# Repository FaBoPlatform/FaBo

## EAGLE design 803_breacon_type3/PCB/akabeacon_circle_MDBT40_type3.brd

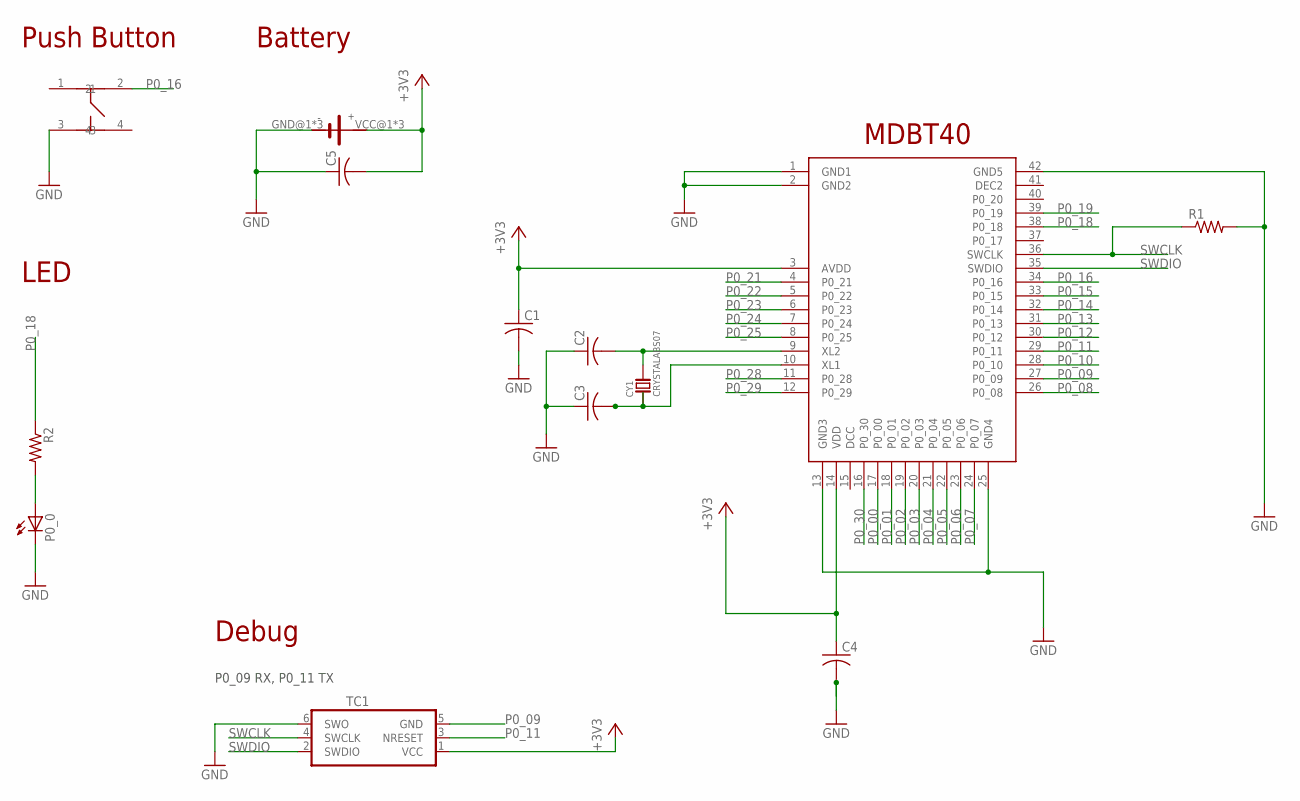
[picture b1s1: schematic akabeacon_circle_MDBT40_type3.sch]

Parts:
C1, C2, C3, C4, C5: C-USC0603; C0603
CY1: CRYSTALABS07; ABRACOM-ABS07-32.768KHZ
P0_0: LEDCHIP-LED0603; CHIP-LED0603
R1, R2: R-US_R0603; R0603
TC1: TC2030-IDC-NL
U$1: RAYTAC-MDBT40
U$3: SQUARE-TYPE3
U$5: SWICTH-4P(KMR2); SWITCH-4P(KMR2)

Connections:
+3V3: C1.1, C4.1, C5.2, TC1.1 (VCC), U$1.3 (AVDD), U$1.14 (VDD), U$3.VCC@1 (VCC), U$3.VCC@2 (VCC), U$3.VCC@3 (VCC)
GND: C1.2, C2.1, C3.1, C4.2, C5.1, P0_0.C, R1.2, TC1.6 (SWO), U$1.1 (GND1), U$1.2 (GND2), U$1.13 (GND3), U$1.25 (GND4), U$1.42 (GND5), U$3.GND@1 (GND), U$3.GND@2 (GND), U$3.GND@3 (GND), U$5.3
unnamed: P0_0.A, R2.2
unnamed: C2.2, CY1.P$2, U$1.9 (XL2)
unnamed: C3.2, CY1.P$1, U$1.10 (XL1)
P0_00: U$1.17 (P0_00)
P0_01: U$1.18 (P0_01)
P0_02: U$1.19 (P0_02)
P0_03: U$1.20 (P0_03)
P0_04: U$1.21 (P0_04)
P0_05: U$1.22 (P0_05)
P0_06: U$1.23 (P0_06)
P0_07: U$1.24 (P0_07)
P0_08: U$1.26 (P0_08)
P0_09: TC1.5 (GND), U$1.27 (P0_09)
P0_10: U$1.28 (P0_10)
P0_11: TC1.3 (NRESET), U$1.29 (P0_11)
P0_12: U$1.30 (P0_12)
P0_13: U$1.31 (P0_13)
P0_14: U$1.32 (P0_14)
P0_15: U$1.33 (P0_15)
P0_16: U$1.34 (P0_16), U$5.2
P0_18: R2.1, U$1.38 (P0_18)
P0_19: U$1.39 (P0_19)
P0_21: U$1.4 (P0_21)
P0_22: U$1.5 (P0_22)
P0_23: U$1.6 (P0_23)
P0_24: U$1.7 (P0_24)
P0_25: U$1.8 (P0_25)
P0_28: U$1.11 (P0_28)
P0_29: U$1.12 (P0_29)
P0_30: U$1.16 (P0_30)
SWCLK: R1.1, TC1.4 (SWCLK), U$1.36 (SWCLK)
SWDIO: TC1.2 (SWDIO), U$1.35 (SWDIO)

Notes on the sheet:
Battery
Push Button
MDBT40
LED
Debug
P0_09 RX, P0_11 TX

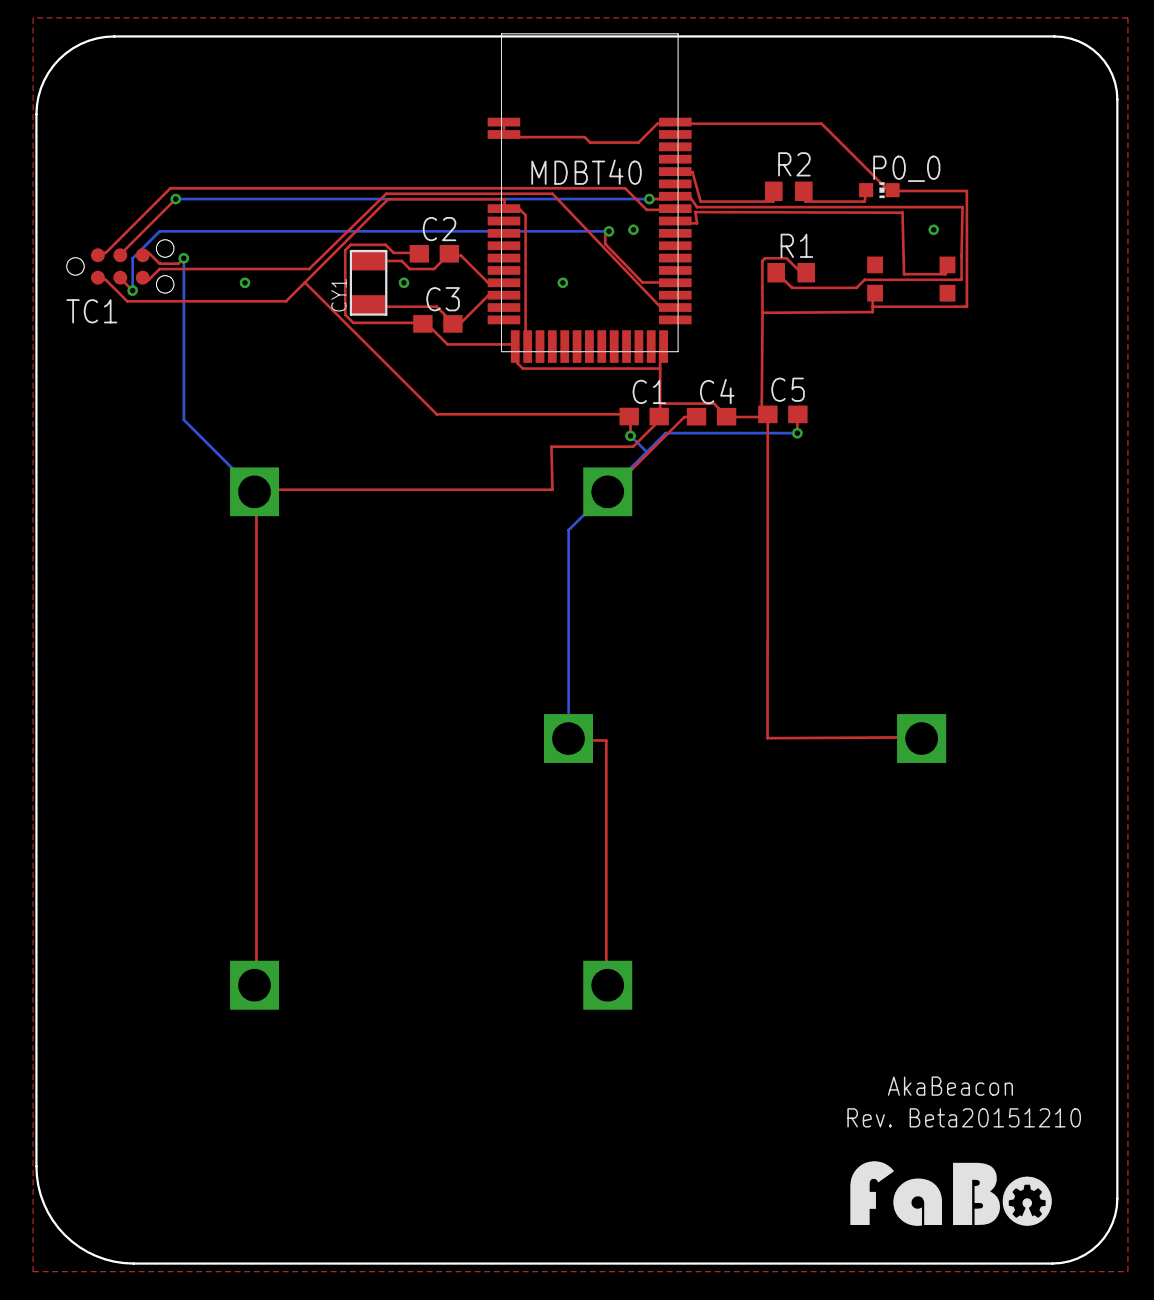
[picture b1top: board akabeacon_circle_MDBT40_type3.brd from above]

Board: 2 copper layers, 61.2 x 69.5 mm, 14 parts (0 on the bottom side), 11 nets.

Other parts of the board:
U$2: LOGO_FABO_M

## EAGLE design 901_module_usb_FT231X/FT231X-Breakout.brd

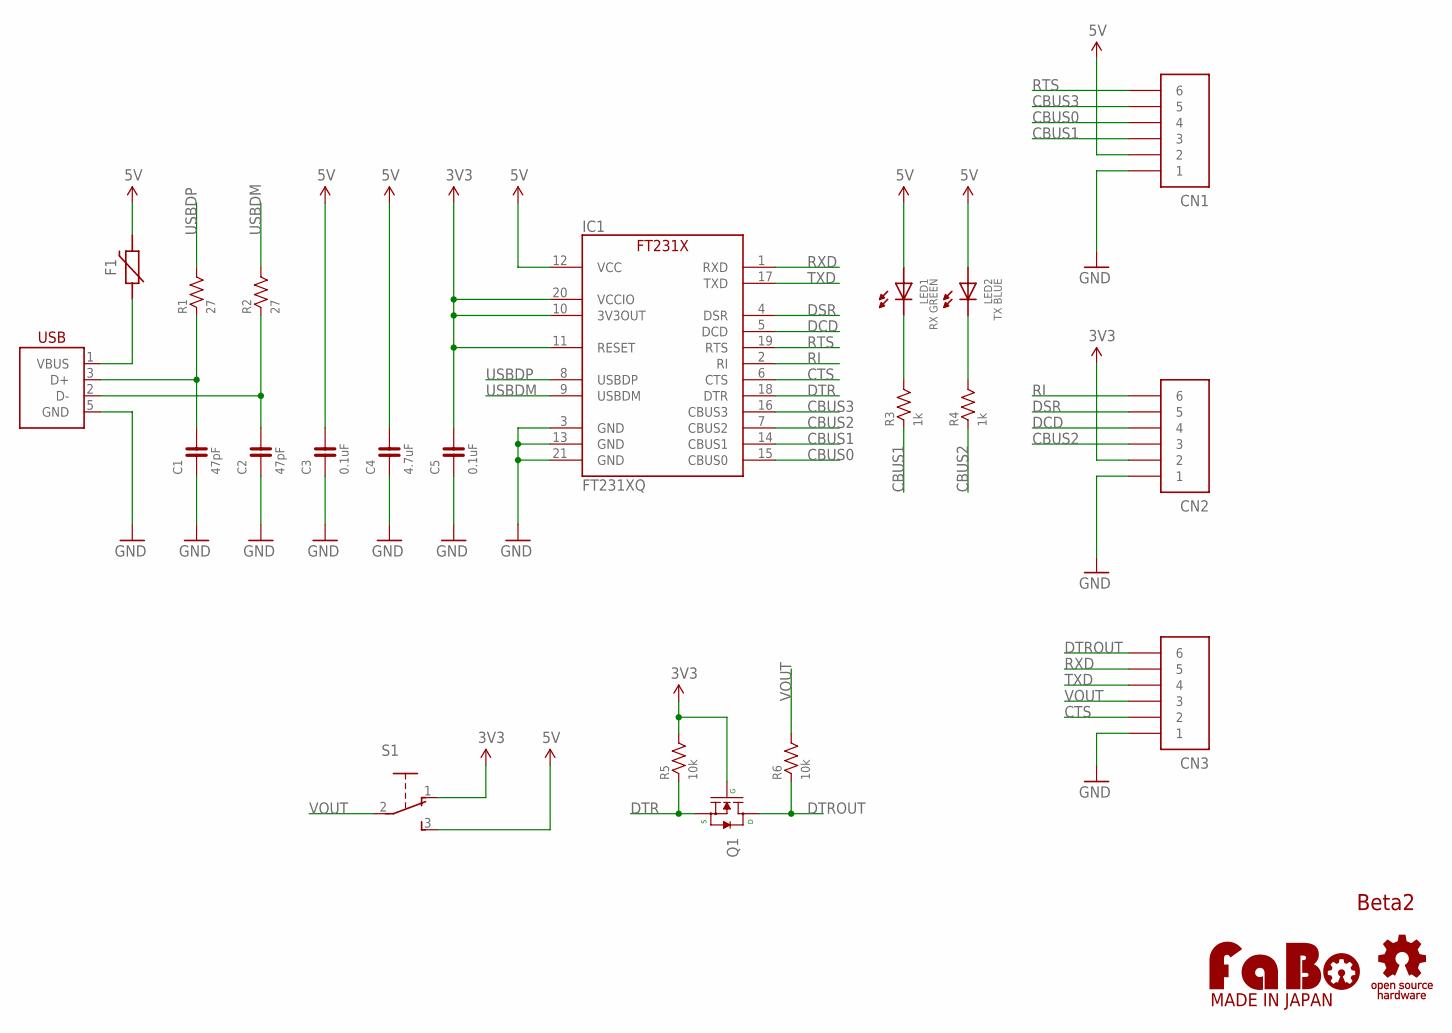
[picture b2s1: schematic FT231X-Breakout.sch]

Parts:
C1, C2: 47pF; 0603-NARROW
C3, C5: 0.1uF; 0603-NARROW
C4: 4.7uF; 0603-NARROW
CN1, CN2, CN3: PIN_HEADER_1X6; PIN_1X6
F1: POLYSWITCH; EIA0603
IC1: FT231XQ; QFN-20_FT231X
LED1: RX GREEN; 0603-NARROW
LED2: TX BLUE; 0603-NARROW
Q1: MOSFET-N; SOT23-3
R1, R2: 27; 0603-NARROW
R3, R4: 1k; 0603-NARROW
R5, R6: 10k; 0603-NARROW
S1: SLIDE-SSSS810701; SSSS810701
U$2: LOGO_FABO-M_BOTTOM; LOGO_FABO_MS_BOTTOM
U$3: LOGO_OSHW-M_BOTTOM; LOGO_OSHW_M_BOTTOM
USB1: USB-MICRO_B_SMT_HIROSE; ZX62R-B-5P

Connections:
3V3: C5.2, CN2.2, IC1.10 (3V3OUT), IC1.11 (RESET), IC1.20 (VCCIO), Q1.1 (G), R5.2, S1.1
5V: C3.2, C4.2, CN1.2, F1.2, IC1.12 (VCC), LED1.ANODE, LED2.ANODE, S1.3
CBUS0: CN1.4, IC1.15 (CBUS0)
CBUS1: CN1.3, IC1.14 (CBUS1), R3.1
CBUS2: CN2.3, IC1.7 (CBUS2), R4.1
CBUS3: CN1.5, IC1.16 (CBUS3)
CTS: CN3.2, IC1.6 (CTS)
DCD: CN2.4, IC1.5 (DCD)
DSR: CN2.5, IC1.4 (DSR)
DTR: IC1.18 (DTR), Q1.2 (S), R5.1
DTROUT: CN3.6, Q1.3 (D), R6.1
GND: C1.1, C2.1, C3.1, C4.1, C5.1, CN1.1, CN2.1, CN3.1, IC1.3 (GND), IC1.13 (GND), IC1.21 (GND), USB1.5 (GND)
unnamed: C2.2, R2.1, USB1.2 (D-)
unnamed: C1.2, R1.1, USB1.3 (D+)
unnamed: LED1.CATHODE, R3.2
unnamed: LED2.CATHODE, R4.2
RI: CN2.6, IC1.2 (RI)
RTS: CN1.6, IC1.19 (RTS)
RXD: CN3.5, IC1.1 (RXD)
TXD: CN3.4, IC1.17 (TXD)
USBDM: IC1.9 (USBDM), R2.2
USBDP: IC1.8 (USBDP), R1.2
VBUS: F1.1, USB1.1 (VBUS)
VOUT: CN3.3, R6.2, S1.2

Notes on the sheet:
Beta2

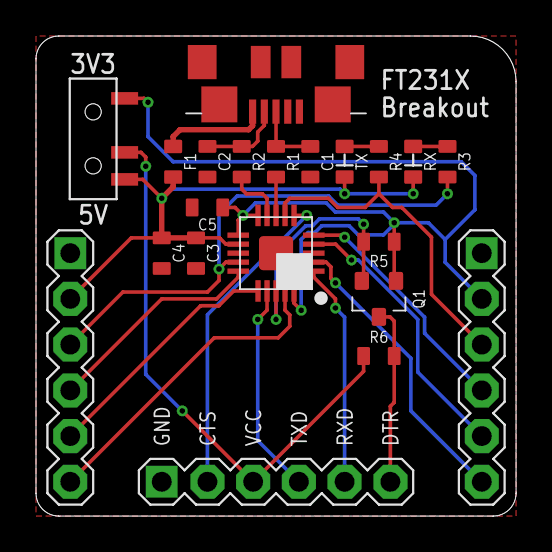
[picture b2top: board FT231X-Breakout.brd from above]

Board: 2 copper layers, 26.7 x 26.7 mm, 23 parts (0 on the bottom side), 24 nets.

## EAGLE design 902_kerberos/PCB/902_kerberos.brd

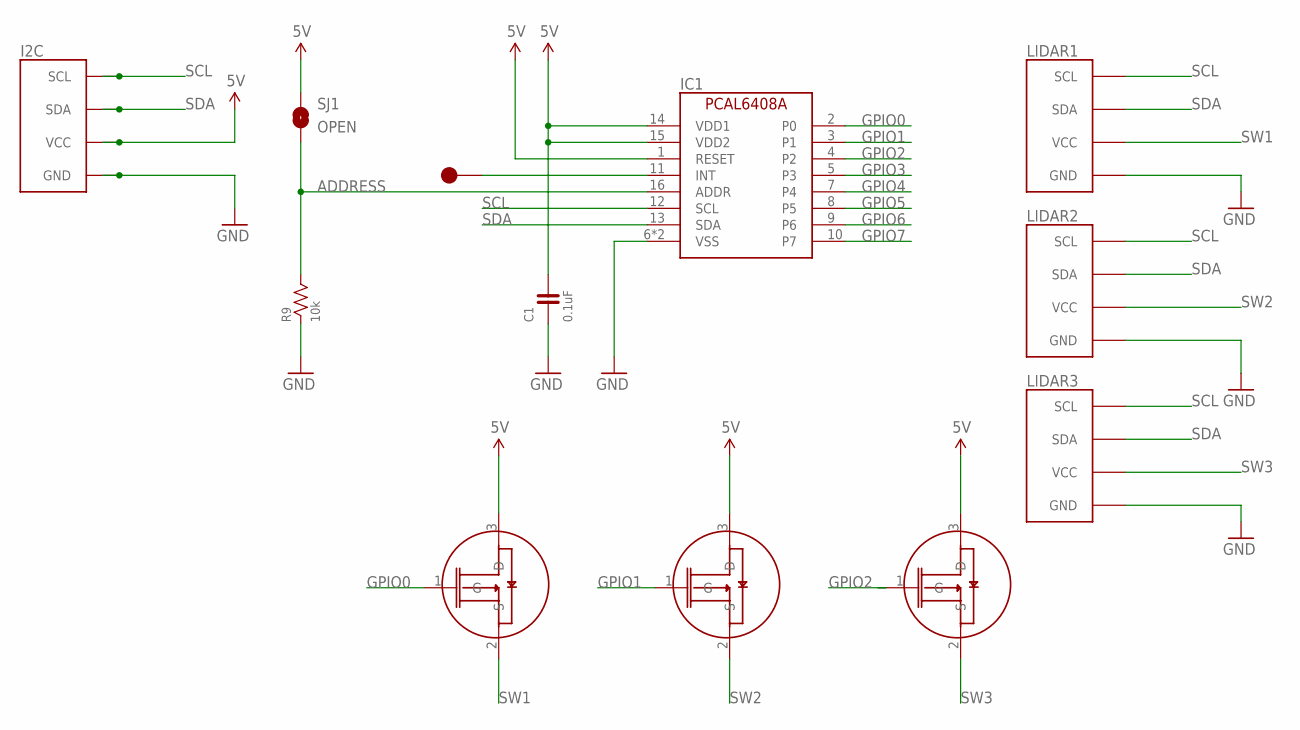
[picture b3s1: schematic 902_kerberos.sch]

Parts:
C1: 0.1uF; 0603
I2C: FABO_BRICK_I2C-S04B-PASK-2; FABO_BRICK_I2C_S04B-PASK-2
IC1: NX-PCAL6408A; NXP-PCAL6408A
LIDAR1, LIDAR2, LIDAR3: FABO_BRICK_I2C-S04B-PASK-2; FABO_BRICK_I2C_S04B-PASK-2
R9: 10k; 0603-NARROW
SJ1: OPEN; SMD-JUMPER-2-OPEN
SW1, SW2, SW3: FAIRCHILD-FDN338; SOT23
TP1: TP-15

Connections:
5V: C1.2, I2C.VCC, IC1.1 (RESET), IC1.14 (VDD1), IC1.15 (VDD2), SJ1.1, SW1.3 (D), SW2.3 (D), SW3.3 (D)
ADDRESS: IC1.16 (ADDR), R9.2, SJ1.2
GND: C1.1, I2C.GND, IC1.6 (VSS), IC1.17 (VSS), LIDAR1.GND, LIDAR2.GND, LIDAR3.GND, R9.1
GPIO0: IC1.2 (P0), SW1.1 (G)
GPIO1: IC1.3 (P1), SW2.1 (G)
GPIO2: IC1.4 (P2), SW3.1 (G)
GPIO3: IC1.5 (P3)
GPIO4: IC1.7 (P4)
GPIO5: IC1.8 (P5)
GPIO6: IC1.9 (P6)
GPIO7: IC1.10 (P7)
INT: IC1.11 (INT), TP1.1
SCL: I2C.SCL, IC1.12 (SCL), LIDAR1.SCL, LIDAR2.SCL, LIDAR3.SCL
SDA: I2C.SDA, IC1.13 (SDA), LIDAR1.SDA, LIDAR2.SDA, LIDAR3.SDA
SW1: LIDAR1.VCC, SW1.2 (S)
SW2: LIDAR2.VCC, SW2.2 (S)
SW3: LIDAR3.VCC, SW3.2 (S)

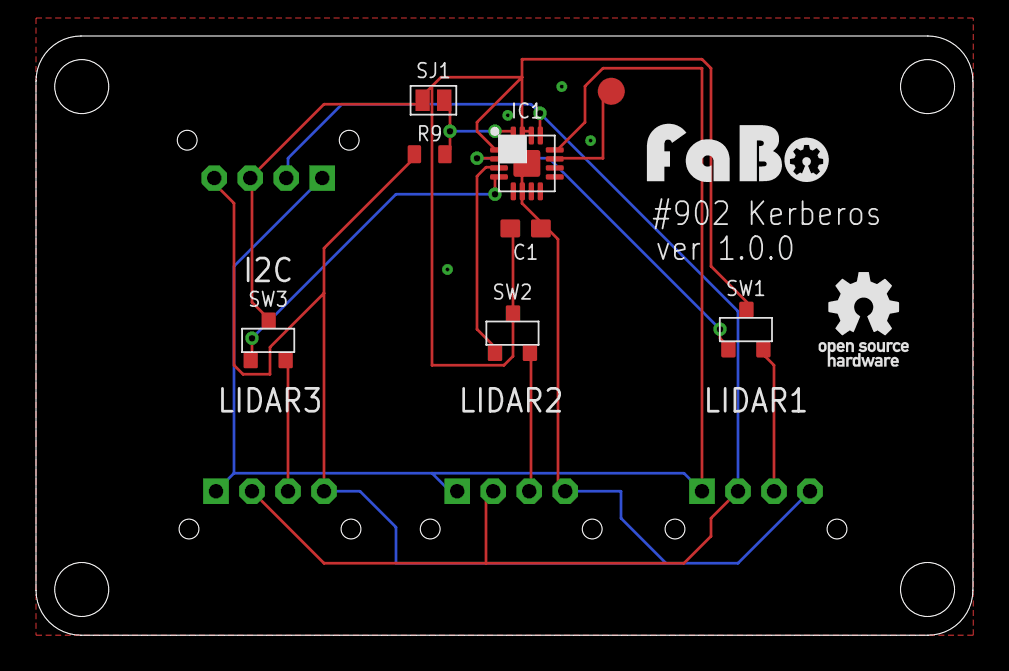
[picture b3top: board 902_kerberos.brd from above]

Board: 2 copper layers, 52.0 x 33.3 mm, 14 parts (0 on the bottom side), 12 nets.

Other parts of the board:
U$2: LOGO_FABO_MS
U$3: LOGO_OSHW_T_MS

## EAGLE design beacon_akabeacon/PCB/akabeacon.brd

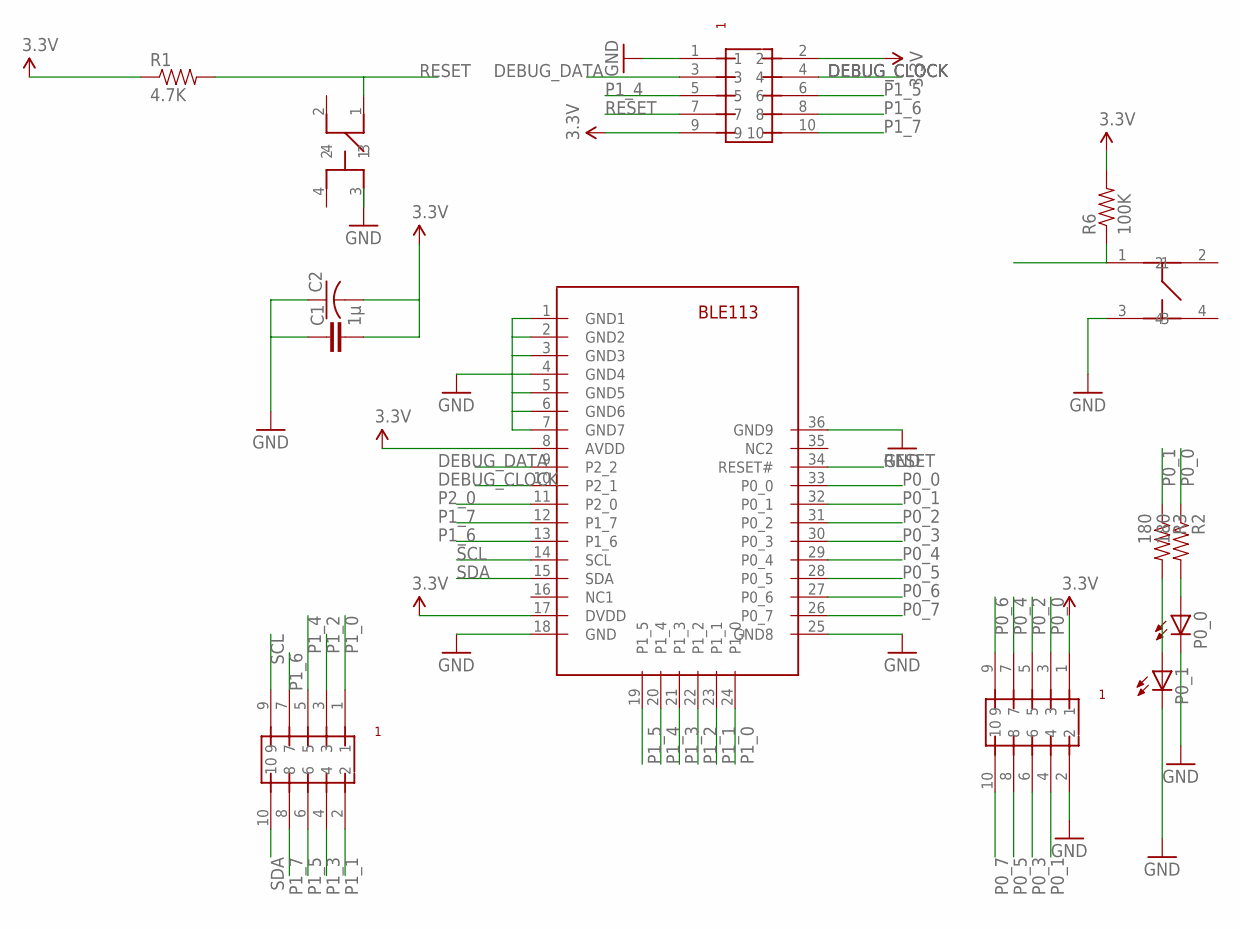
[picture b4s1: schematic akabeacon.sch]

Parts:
C1: 1μ; 0603-CAP
C2: C-USC3225; C3225
P0_0, P0_1: LEDCHIP-LED0603; CHIP-LED0603
R1: 4.7K; 0603-RES
R2, R3: 180; 0603-RES
R6: 100K; 0603-RES
U$1: SWICTH-4P(KMR2); SWITCH-4P(KMR2)
U$2, U$3, U$4: PIN-HEADER-SMT(1.27MM)2X5
U$5: BLE113
U$8: SWITCH-LS6J2M-T; SWICTH-LS6J2M-T

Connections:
3.3V: C1.2, C2.2, R1.1, R6.2, U$2.2, U$2.9, U$4.1, U$5.8 (AVDD), U$5.17 (DVDD)
DEBUG_CLOCK: U$2.4, U$5.10 (P2_1)
DEBUG_DATA: U$2.3, U$5.9 (P2_2)
GND: C1.1, C2.1, P0_0.C, P0_1.C, U$1.3, U$2.1, U$4.2, U$5.1 (GND1), U$5.2 (GND2), U$5.3 (GND3), U$5.4 (GND4), U$5.5 (GND5), U$5.6 (GND6), U$5.7 (GND7), U$5.18 (GND), U$5.25 (GND8), U$5.36 (GND9), U$8.3
unnamed: P0_0.A, R2.2
unnamed: P0_1.A, R3.2
P0_0: R2.1, U$4.3, U$5.33 (P0_0)
P0_1: R3.1, U$4.4, U$5.32 (P0_1)
P0_2: U$4.5, U$5.31 (P0_2)
P0_3: U$4.6, U$5.30 (P0_3)
P0_4: U$4.7, U$5.29 (P0_4)
P0_5: U$4.8, U$5.28 (P0_5)
P0_6: U$4.9, U$5.27 (P0_6)
P0_7: U$4.10, U$5.26 (P0_7)
P0_8: R6.1, U$1.1
P1_0: U$3.1, U$5.24 (P1_0)
P1_1: U$3.2, U$5.23 (P1_1)
P1_2: U$3.3, U$5.22 (P1_2)
P1_3: U$3.4, U$5.21 (P1_3)
P1_4: U$2.5, U$3.5, U$5.20 (P1_4)
P1_5: U$2.6, U$3.6, U$5.19 (P1_5)
P1_6: U$2.8, U$3.7, U$5.13 (P1_6)
P1_7: U$2.10, U$3.8, U$5.12 (P1_7)
P2_0: U$5.11 (P2_0)
RESET: R1.2, U$2.7, U$5.34 (RESET#), U$8.1
SCL: U$3.9, U$5.14 (SCL)
SDA: U$3.10, U$5.15 (SDA)

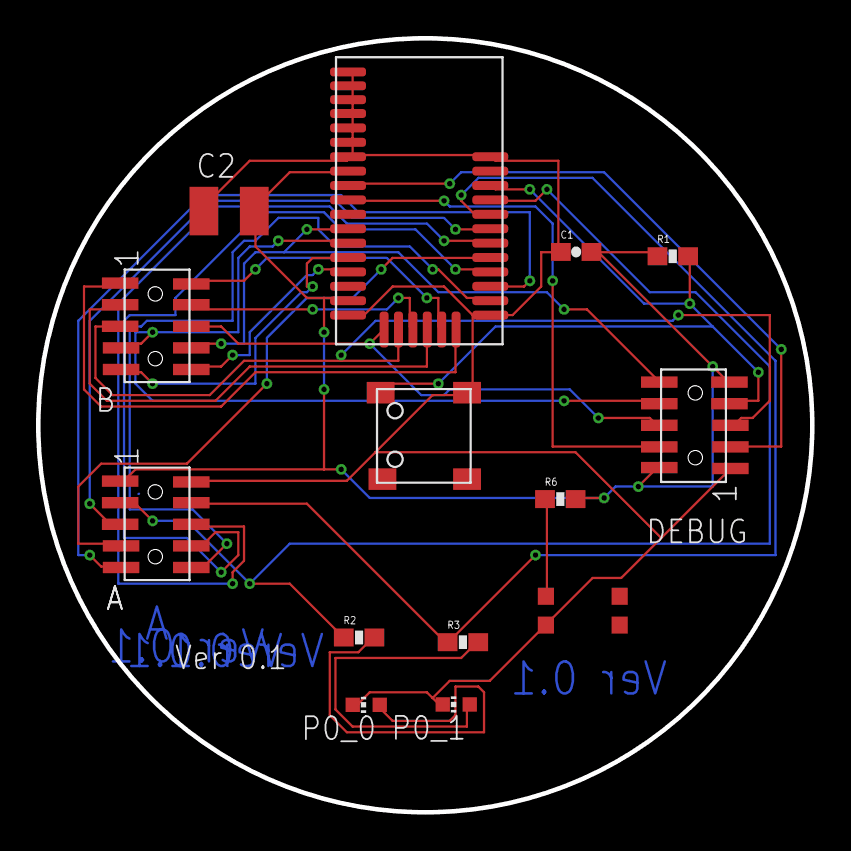
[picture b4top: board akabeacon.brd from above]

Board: 4 copper layers, 43.0 x 43.0 mm, 14 parts (0 on the bottom side), 26 nets.

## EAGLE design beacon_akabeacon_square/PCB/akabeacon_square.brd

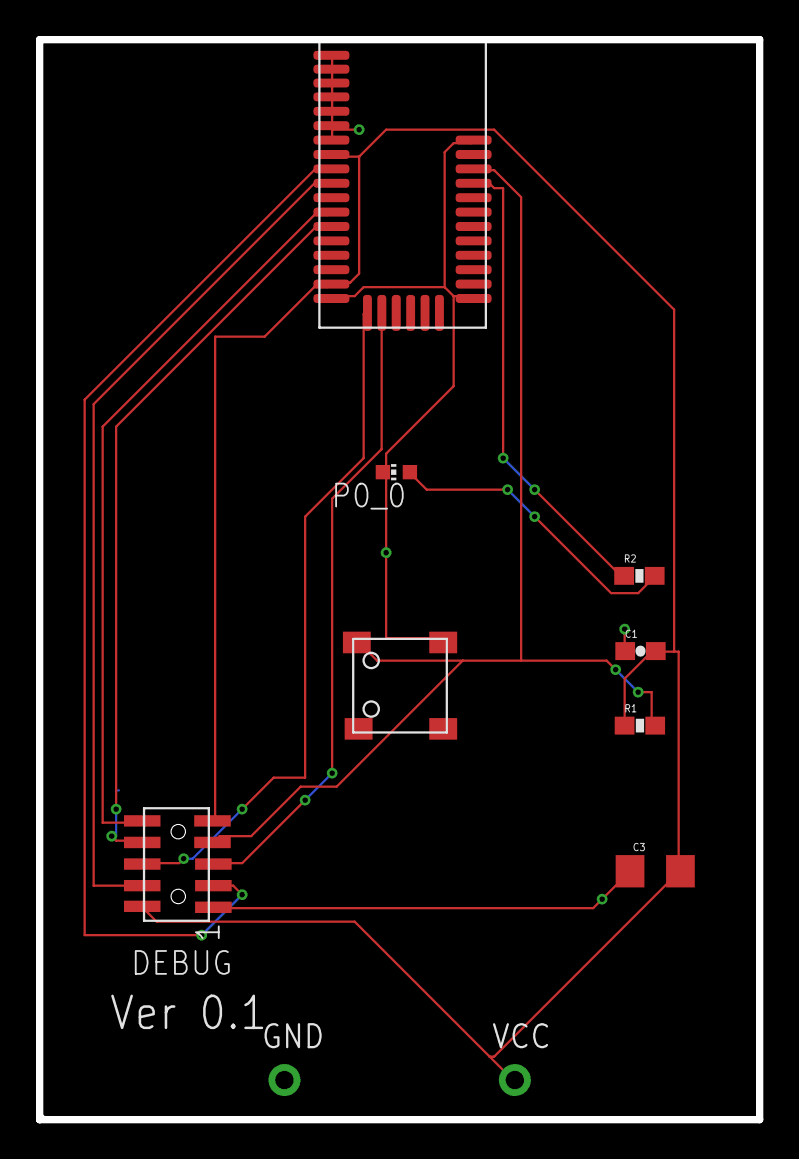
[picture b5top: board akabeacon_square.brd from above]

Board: 4 copper layers, 40.0 x 60.0 mm, 10 parts (0 on the bottom side), 11 nets.

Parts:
C1: 1μ; 0603-CAP
C3: 100uF; 1206
GND: 1X01-CLEANBIG
P0_0: CHIP-LED0603
R1: 4.7K; 0603-RES
R2: 180; 0603-RES
U$2: PIN-HEADER-SMT(1.27MM)2X5
U$5: BLE113
U$8: SWITCH-LS6J2M-T; SWICTH-LS6J2M-T
VCC: 1X01-CLEANBIG

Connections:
3.3V: C1.2, C3.2, R1.1, U$2.2, U$2.9, U$5.8, U$5.17, VCC.1
DEBUG_CLOCK: U$2.4, U$5.10
DEBUG_DATA: U$2.3, U$5.9
GND: C1.1, C3.1, GND.1, P0_0.C, U$2.1, U$5.1, U$5.2, U$5.3, U$5.4, U$5.5, U$5.6, U$5.7, U$5.18, U$5.25, U$5.36, U$8.3
unnamed: P0_0.A, R2.2
P0_0: R2.1, U$5.33
P1_4: U$2.5, U$5.20
P1_5: U$2.6, U$5.19
P1_6: U$2.8, U$5.13
P1_7: U$2.10, U$5.12
RESET: R1.2, U$2.7, U$5.34, U$8.1

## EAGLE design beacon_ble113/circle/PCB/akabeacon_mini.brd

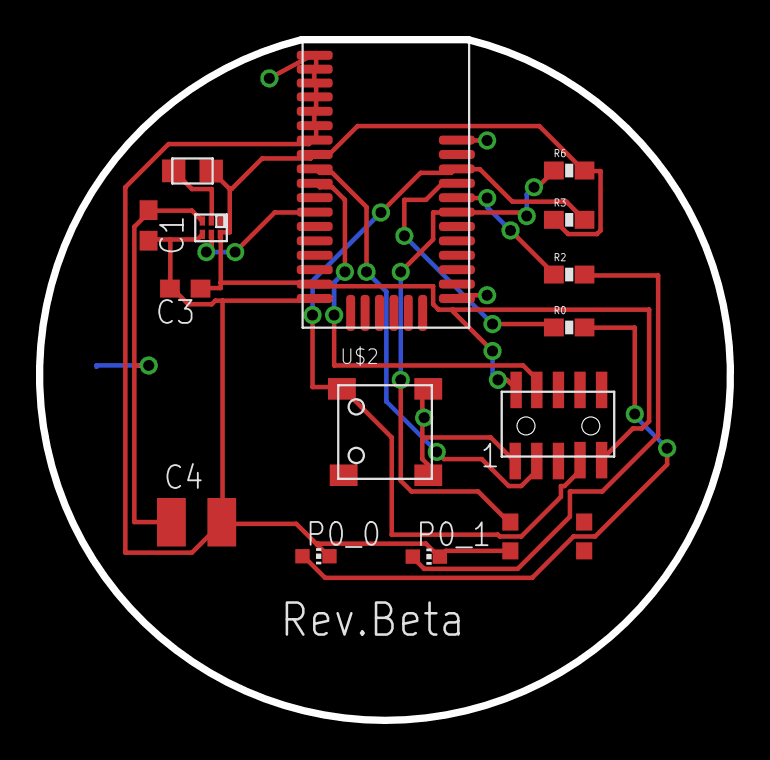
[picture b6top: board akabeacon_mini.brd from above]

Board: 2 copper layers, 38.4 x 37.8 mm, 16 parts (0 on the bottom side), 13 nets.

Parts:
C1, C3: C0603
C4: C3225
INDUCTOR1: INDUCTOR-0805
P0_0, P0_1: CHIP-LED0603
R0, R2: 180OHM; 0603-RES
R3: 10K; 0603-RES
R6: 100K; 0603-RES
TPS1: TI-TPS62730
U$1: SMTU2450-BOTTOM-MINI
U$2: SWITCH-LS6J2M-T
U$3: PIN-HEADER-SMT(1.27MM)2X5
U$4: BLE113
U$5: SWICTH-4P(KMR2); SWITCH-4P(KMR2)

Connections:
DEBUG_CLOCK: U$3.4, U$4.10
DEBUG_DATA: U$3.3, U$4.9
GND: C1.2, C3.2, C4.2, P0_0.C, P0_1.C, TPS1.4, U$1.P$_GND, U$2.3, U$2.4, U$3.1, U$4.1, U$4.2, U$4.3, U$4.4, U$4.5, U$4.6, U$4.7, U$4.18, U$4.25, U$4.36, U$5.3
unnamed: C1.1, C4.1, TPS1.3, U$1.P$_VCC
unnamed: P0_0.A, R0.2
unnamed: P0_1.A, R2.2
unnamed: INDUCTOR1.P$1, TPS1.2
P0_0: R0.1, U$4.33
P0_1: R2.1, U$4.32
P0_2: R6.1, U$4.31, U$5.1
P1_7: TPS1.5, U$4.12
RESET: R3.2, U$2.1, U$3.7, U$4.34
V+: C3.1, INDUCTOR1.P$2, R3.1, R6.2, TPS1.6, U$3.2, U$3.9, U$4.8, U$4.17

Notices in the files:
parts and their libraries:
FaBo-Template: Released under the Creative Commons Attribution-ShareAlike 4.0 License
https://creativecommons.org/licenses/by-sa/4.0
gclue: Released under the Creative Commons
SparkFun: Licensing: CC v3.0 Share-Alike You are welcome to use this library for commercial purposes.
